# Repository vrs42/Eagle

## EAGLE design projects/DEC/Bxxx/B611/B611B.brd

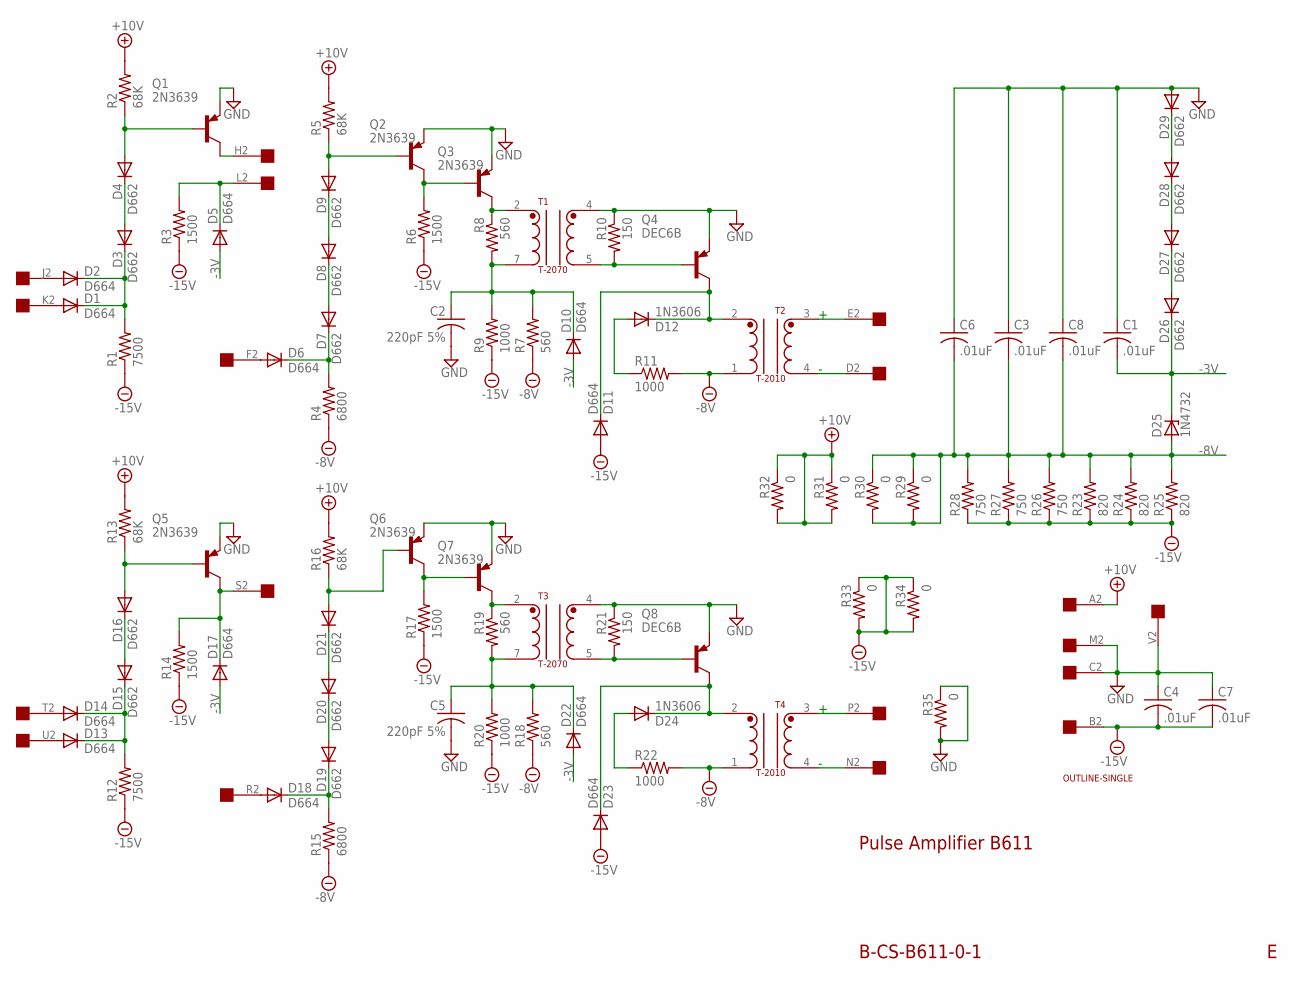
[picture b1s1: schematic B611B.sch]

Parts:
C1, C3, C4, C6, C7, C8: .01uF; C063-025X075
C2, C5: 220pF 5%; C150-054X183
D1, D2, D5, D6, D10, D11, D13, D14, D17, D18, D22, D23: D664; DO35-10
D3, D4, D7, D8, D9, D15, D16, D19, D20, D21, D26, D27, D28, D29: D662; DO35-10
D12, D24: 1N3606; DO35-10
D25: 1N4732; DO35Z10
Q1, Q2, Q3, Q5, Q6, Q7: 2N3639; TO39
Q4, Q8: DEC6B; TO39
R1, R12: 7500; 0207/10
R2, R5, R13, R16: 68K; 0207/10
R3, R6, R14, R17: 1500; 0207/10
R4, R15: 6800; 0207/10
R7, R8, R18, R19: 560; 0207/10
R9, R11, R20, R22: 1000; 0207/10
R10, R21: 150; 0207/10
R23, R24, R25: 820; 0207/10
R26, R27, R28: 750; 0207/10
R29, R30, R31, R32, R33, R34, R35: 0; 0207/10
T1, T3: T-2070; TRANSFORMER
T2, T4: T-2010; TRANSFORMER2
U$1: OUTLINE-SINGLE; SINGLE
U$2: EDGE-1; EDGE-CON1

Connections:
+10V: R2.2, R5.2, R13.2, R16.2, R31.1, R31.2, R32.1, R32.2, U$2.A2
-3V: C1.2, D5.A, D10.A, D17.A, D22.A, D25.C, D26.C
-8V: C3.2, C6.2, C8.2, D25.A, R4.1, R7.1, R11.2, R15.1, R18.1, R22.2, R23.2, R24.2, R25.2, R26.2, R27.2, R28.2, R29.1, R29.2, R30.1, R30.2, T2.1, T4.1
-15V: C4.2, C7.2, D11.A, D23.A, R1.1, R3.1, R6.1, R9.1, R12.1, R14.1, R17.1, R20.1, R23.1, R24.1, R25.1, R26.1, R27.1, R28.1, R33.1, R33.2, R34.1, R34.2, U$2.B2
GND: C1.1, C2.2, C3.1, C4.1, C5.2, C6.1, C7.1, C8.1, D29.A, Q1.1 (E), Q2.1 (E), Q3.1 (E), Q4.1 (E), Q5.1 (E), Q6.1 (E), Q7.1 (E), Q8.1 (E), R10.1, R21.1, R35.1, R35.2, T1.4, T3.4, U$2.C2, U$2.M2, U$2.V2
unnamed: D16.A, Q5.2 (B), R13.1
unnamed: D12.A, R11.1
unnamed: T2.3, U$2.E2
unnamed: T2.4, U$2.D2
unnamed: Q2.3 (C), Q3.2 (B), R6.2
unnamed: D11.C, D12.C, Q4.3 (C), T2.2
unnamed: D9.A, Q2.2 (B), R5.1
unnamed: C2.1, D10.C, R7.2, R8.2, R9.2, T1.7
unnamed: Q4.2 (B), R10.2, T1.5
unnamed: D8.A, D9.C
unnamed: D7.A, D8.C
unnamed: D6.C, D7.C, R4.2
unnamed: D6.A, U$2.F2
unnamed: Q3.3 (C), R8.1, T1.2
unnamed: D5.C, R3.2, U$2.L2
unnamed: Q1.3 (C), U$2.H2
unnamed: D2.A, U$2.J2
unnamed: D1.C, D2.C, D3.C, R1.2
unnamed: D4.A, Q1.2 (B), R2.1
unnamed: D3.A, D4.C
unnamed: D1.A, U$2.K2
unnamed: D17.C, Q5.3 (C), R14.2, U$2.S2
unnamed: D21.A, Q6.2 (B), R16.1
unnamed: D13.C, D14.C, D15.C, R12.2
unnamed: D15.A, D16.C
unnamed: D28.A, D29.C
unnamed: D27.A, D28.C
unnamed: D14.A, U$2.T2
unnamed: D26.A, D27.C
unnamed: D13.A, U$2.U2
unnamed: D20.A, D21.C
unnamed: D19.A, D20.C
unnamed: D18.C, D19.C, R15.2
unnamed: D18.A, U$2.R2
unnamed: T4.3, U$2.P2
unnamed: T4.4, U$2.N2
unnamed: D23.C, D24.C, Q8.3 (C), T4.2
unnamed: C5.1, D22.C, R18.2, R19.2, R20.2, T3.7
unnamed: Q8.2 (B), R21.2, T3.5
unnamed: Q7.3 (C), R19.1, T3.2
unnamed: D24.A, R22.1
unnamed: Q6.3 (C), Q7.2 (B), R17.2

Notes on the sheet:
Pulse Amplifier B611
B-CS-B611-0-1

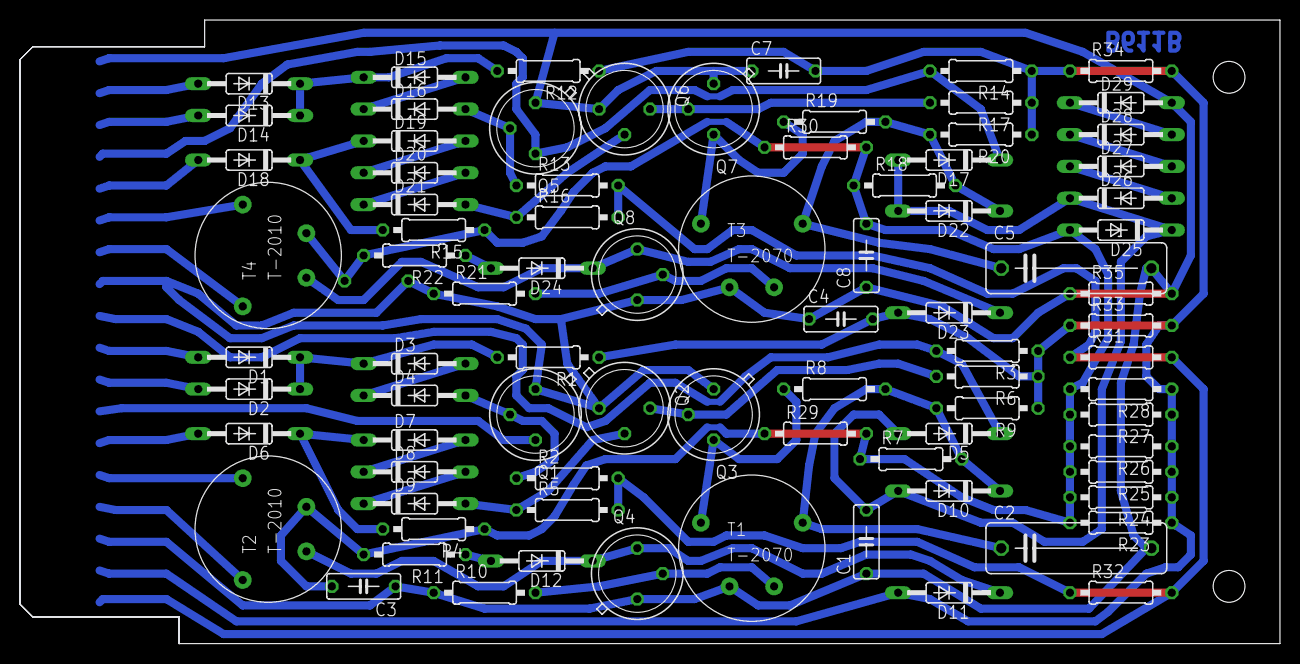
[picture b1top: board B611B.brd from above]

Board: 2 copper layers, 125.7 x 62.2 mm, 86 parts (1 on the bottom side), 47 nets.

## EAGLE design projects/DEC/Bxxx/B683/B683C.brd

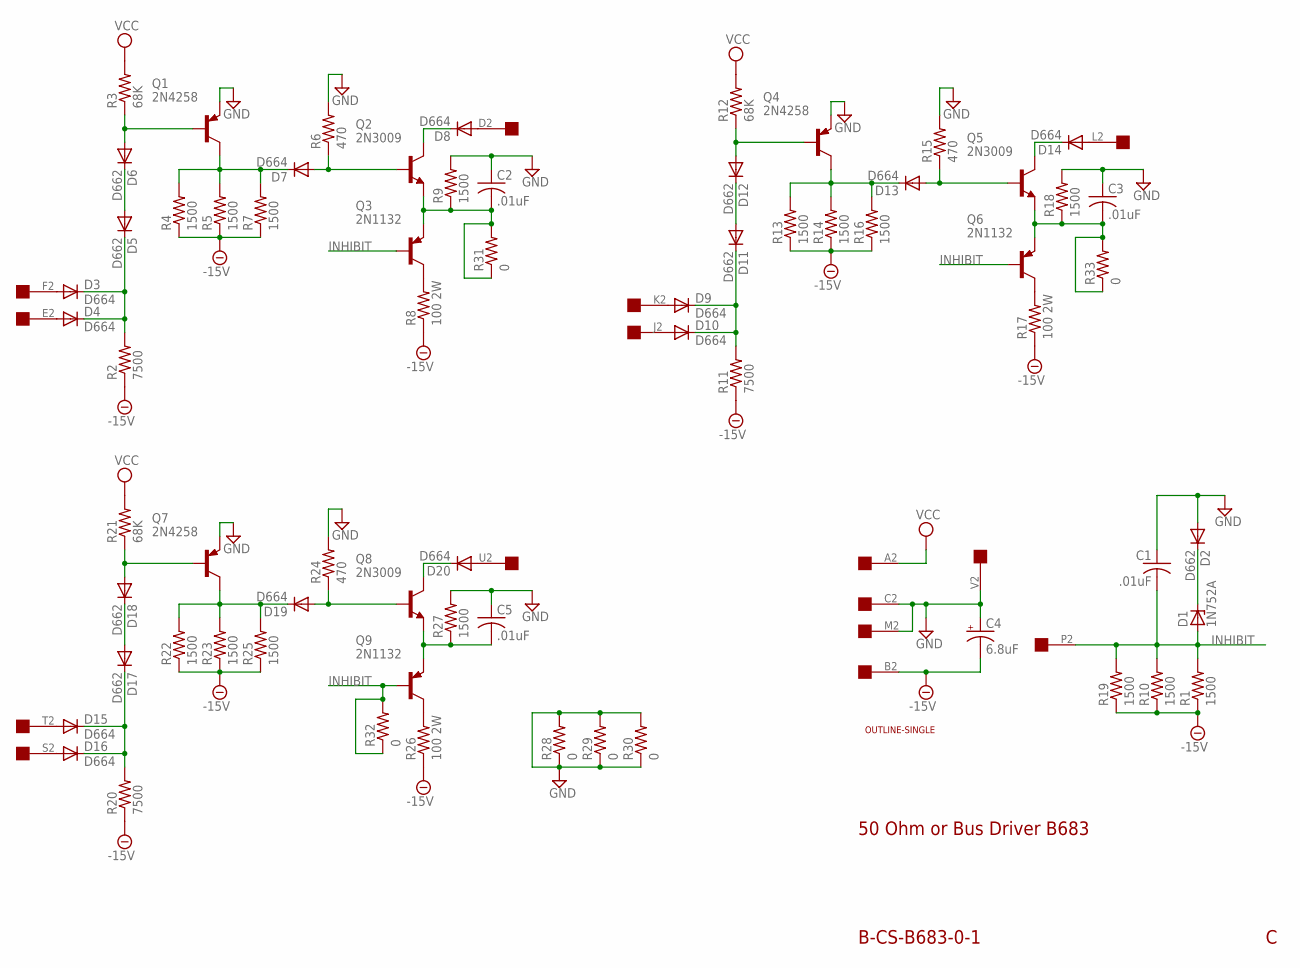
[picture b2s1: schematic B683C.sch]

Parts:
C1, C2, C3, C5: .01uF; C063-025X075
C4: 6.8uF; E12-8
D1: 1N752A; DO35Z10
D2, D5, D6, D11, D12, D17, D18: D662; DO35-10
D3, D4, D7, D8, D9, D10, D13, D14, D15, D16, D19, D20: D664; DO35-10
Q1, Q4, Q7: 2N4258; TO5
Q2, Q5, Q8: 2N3009; TO5
Q3, Q6, Q9: 2N1132; TO5
R1, R4, R5, R7, R9, R10, R13, R14, R16, R18, R19, R22, R23, R25, R27: 1500; 0207/10
R2, R11, R20: 7500; 0207/10
R3, R12, R21: 68K; 0207/10
R6, R15, R24: 470; 0207/10
R8, R17, R26: 100 2W; 0818/25
R28, R29, R30, R31, R32, R33: 0; 0207/10
U$1: OUTLINE-SINGLE; SINGLE
U$2: EDGE-1; EDGE-CON1

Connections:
-15V: C4.-, R1.1, R2.1, R4.1, R5.1, R7.1, R8.1, R10.1, R11.1, R13.1, R14.1, R16.1, R17.1, R19.1, R20.1, R22.1, R23.1, R25.1, R26.1, U$2.B2
GND: C1.1, C2.1, C3.1, C4.+, C5.1, D2.A, Q1.1 (E), Q4.1 (E), Q7.1 (E), R6.2, R9.2, R15.2, R18.2, R24.2, R27.2, R28.1, R28.2, R29.1, R29.2, R30.1, R30.2, U$2.C2, U$2.M2, U$2.V2
INHIBIT: C1.2, D1.A, Q3.2 (B), Q6.2 (B), Q9.2 (B), R1.2, R10.2, R19.2, R32.1, R32.2, U$2.P2
unnamed: D6.A, Q1.2 (B), R3.1
unnamed: D1.C, D2.C
unnamed: D3.C, D4.C, D5.C, R2.2
unnamed: D5.A, D6.C
unnamed: D7.C, Q1.3 (C), R4.2, R5.2, R7.2
unnamed: D7.A, Q2.2 (B), R6.1
unnamed: D8.C, Q2.3 (C)
unnamed: C2.2, Q2.1 (E), Q3.1 (E), R9.1, R31.1, R31.2
unnamed: Q3.3 (C), R8.2
unnamed: D12.A, Q4.2 (B), R12.1
unnamed: D9.C, D10.C, D11.C, R11.2
unnamed: D11.A, D12.C
unnamed: D13.C, Q4.3 (C), R13.2, R14.2, R16.2
unnamed: D13.A, Q5.2 (B), R15.1
unnamed: D14.C, Q5.3 (C)
unnamed: C3.2, Q5.1 (E), Q6.1 (E), R18.1, R33.1, R33.2
unnamed: Q6.3 (C), R17.2
unnamed: D18.A, Q7.2 (B), R21.1
unnamed: D15.C, D16.C, D17.C, R20.2
unnamed: D17.A, D18.C
unnamed: D19.C, Q7.3 (C), R22.2, R23.2, R25.2
unnamed: D19.A, Q8.2 (B), R24.1
unnamed: D20.C, Q8.3 (C)
unnamed: C5.2, Q8.1 (E), Q9.1 (E), R27.1
unnamed: Q9.3 (C), R26.2
unnamed: D8.A, U$2.D2
unnamed: D3.A, U$2.F2
unnamed: D4.A, U$2.E2
unnamed: D9.A, U$2.K2
unnamed: D10.A, U$2.J2
unnamed: D14.A, U$2.L2
unnamed: D20.A, U$2.U2
unnamed: D15.A, U$2.T2
unnamed: D16.A, U$2.S2
VCC: R3.2, R12.2, R21.2, U$2.A2

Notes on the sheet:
B-CS-B683-0-1
50 Ohm or Bus Driver B683

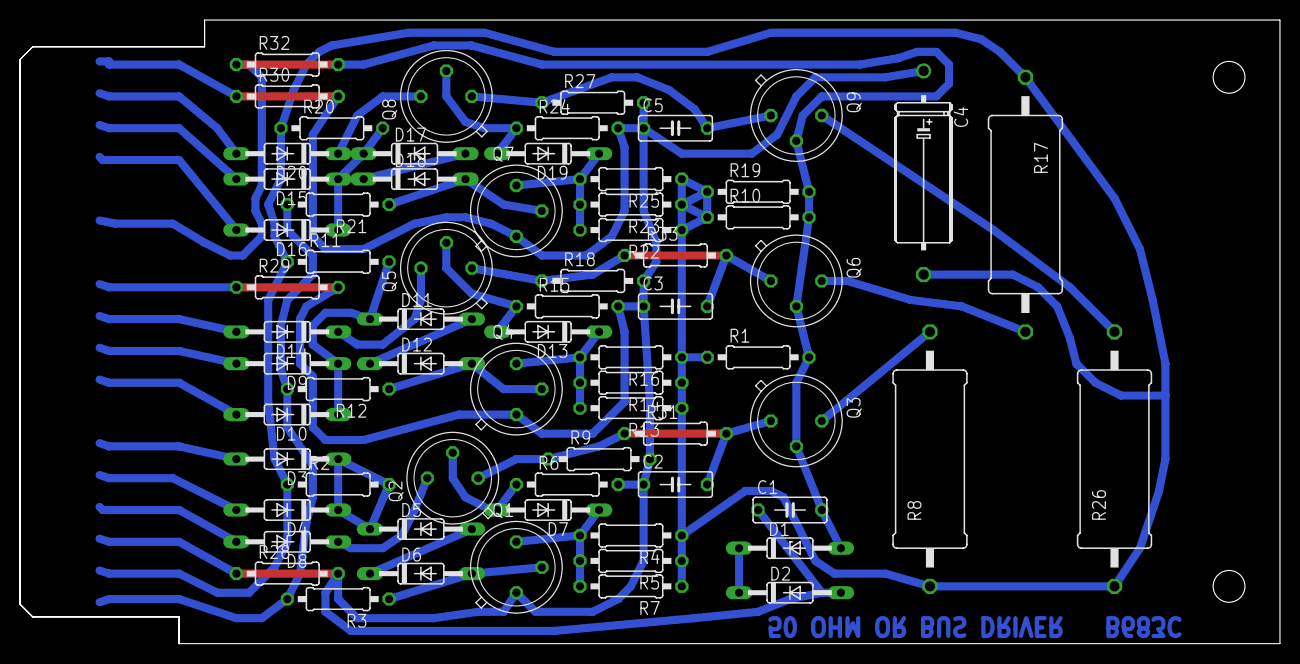
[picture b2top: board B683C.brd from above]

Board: 2 copper layers, 125.7 x 62.2 mm, 69 parts (0 on the bottom side), 38 nets.

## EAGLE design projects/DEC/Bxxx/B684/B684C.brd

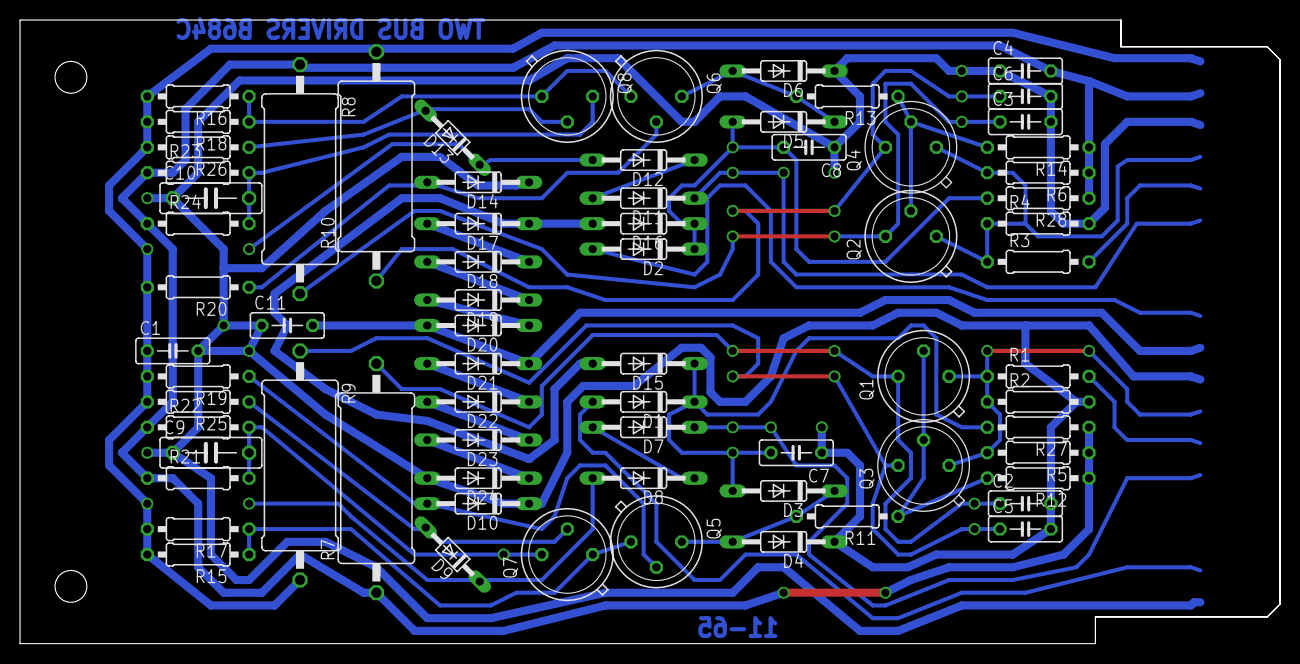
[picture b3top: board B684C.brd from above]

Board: 2 copper layers, 125.7 x 62.2 mm, 73 parts (0 on the bottom side), 41 nets.

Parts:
C1, C2, C3, C4, C5, C6, C7, C8, C11: .01uF; C050-025X075
C9, C10: 56pF; C075-032X103
D1, D2, D3, D4, D5, D6, D15, D16: 1N3606; DO35-10
D7, D8, D10, D11, D12, D14, D17, D18, D19, D20, D21, D22, D23, D24: 1N645; DO35-10
D9, D13: 1N645; DO34-7
Q1, Q2: 2N2904; TO39
Q3, Q4: 2N2219; TO5
Q5, Q6, Q7, Q8: DEC6; TO39
R1, R3: 82; 0207/10
R2, R4: 220 5%; 0207/10
R5, R6, R12, R14: 1.5K 5%; 0207/10
R7, R8: 100 2W; P0817/22
R9, R10: 150 2W; P0817/22
R11, R13: 10; 0207/10
R15, R16, R17, R18: 750 5%; 0207/10
R19, R20: 12K; 0207/10
R21, R22, R23, R24: 560; 0207/10
R25, R26: 100K; 0207/10
R27, R28: 1500 5%; 0207/10
U$1: OUTLINE-SINGLE; SINGLE
U$2: EDGE-1; EDGE-CON1

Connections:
+10V: C1.1, R9.2, R10.2, R15.2, R16.2, R17.2, R18.2, R19.2, R20.2, R25.2, R26.2, U$2.A2
-3V: C11.2, D20.A, D21.C, U$2.L2
-6V@1: C7.2, D1.C, D3.A, D15.C, R27.2
-6V@2: C8.2, D2.C, D5.A, D16.C, R28.2
-15V: C4.2, R5.1, R6.1, R7.1, R8.1, R12.1, R14.1, R21.1, R22.1, R23.1, R24.1, R27.1, R28.1, U$2.B2
GND: C1.2, C2.2, C3.2, C4.1, C5.2, C6.2, C7.1, C8.1, C9.1, C10.1, C11.1, D4.C, D6.C, D10.C, D14.C, D24.A, R2.2, R4.2, U$2.C2, U$2.M2, U$2.V2
unnamed: D11.C, U$2.F2
unnamed: D11.A, D12.C
unnamed: D13.A, Q8.2, R26.1
unnamed: D12.A, D13.C
unnamed: C10.2, Q8.3, R23.2, R24.2
unnamed: Q6.1, Q8.1, R16.1, R18.1
unnamed: D14.A, Q6.2, R20.1
unnamed: Q2.1, Q4.1, R3.1, R4.1, R6.2, U$2.D2
unnamed: C6.1, Q4.3, R10.1
unnamed: C3.1, Q2.3, R8.2
unnamed: D18.A, D19.C
unnamed: D22.A, D23.C
unnamed: D5.C, D6.A, Q6.3, R13.2
unnamed: Q2.2, Q4.2, R13.1, R14.2
unnamed: D21.A, D22.C
unnamed: D2.A, U$2.K2
unnamed: R3.2, U$2.E2
unnamed: D7.C, U$2.R2
unnamed: D17.A, D18.C
unnamed: D7.A, D8.C
unnamed: D8.A, D9.C
unnamed: D9.A, Q7.2, R25.1
unnamed: D19.A, D20.C
unnamed: C9.2, Q7.3, R21.2, R22.2
unnamed: Q5.1, Q7.1, R15.1, R17.1
unnamed: D10.A, Q5.2, R19.1
unnamed: D3.C, D4.A, Q5.3, R11.2
unnamed: Q1.2, Q3.2, R11.1, R12.2
unnamed: D1.A, U$2.U2
unnamed: D15.A, D16.A, D17.C
unnamed: Q1.1, Q3.1, R1.1, R2.1, R5.2, U$2.N2
unnamed: C5.1, Q3.3, R9.1
unnamed: C2.1, Q1.3, R7.2
unnamed: R1.2, U$2.P2
unnamed: D23.A, D24.C
